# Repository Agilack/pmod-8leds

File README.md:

PMOD 8 Leds
===========

This project is a PMOD prototyping board with 8 LEDs.

 | 
------------------- | -------------------------------

The board connector use a PMOD type 1A pinout. Each available GPIO is
connected to one LED with a component id that reflect signel id (LED D1 is
mapped to signal GPIO1, D2 for GPIO2 ...)
To avoid driving too much current from host ios, a buffer is placed between
connector and LEDs. This buffer add a small latency (~5ns) and limit the
switching frequency to fwe dozen MHz but this seem to be acceptable for
LEDs ;)

Designed with Kicad
-------------------
This board has been designed using Kicad 5.0.2
For a better compatibility and a simplified distribution of this project,
all schematics components are available into a custom project library. It's
the same for board footprints that have been saved into a cutom library. For
3D models, default kicad parts are used (and some display errors can occurs)

 |  | 
------------------------- | ------------------------- | ---------------------------------

License
-------

This project is licensed under a [Creative Commons Attribution-ShareAlike 4.0 International License](http://creativecommons.org/licenses/by-sa/4.0/).

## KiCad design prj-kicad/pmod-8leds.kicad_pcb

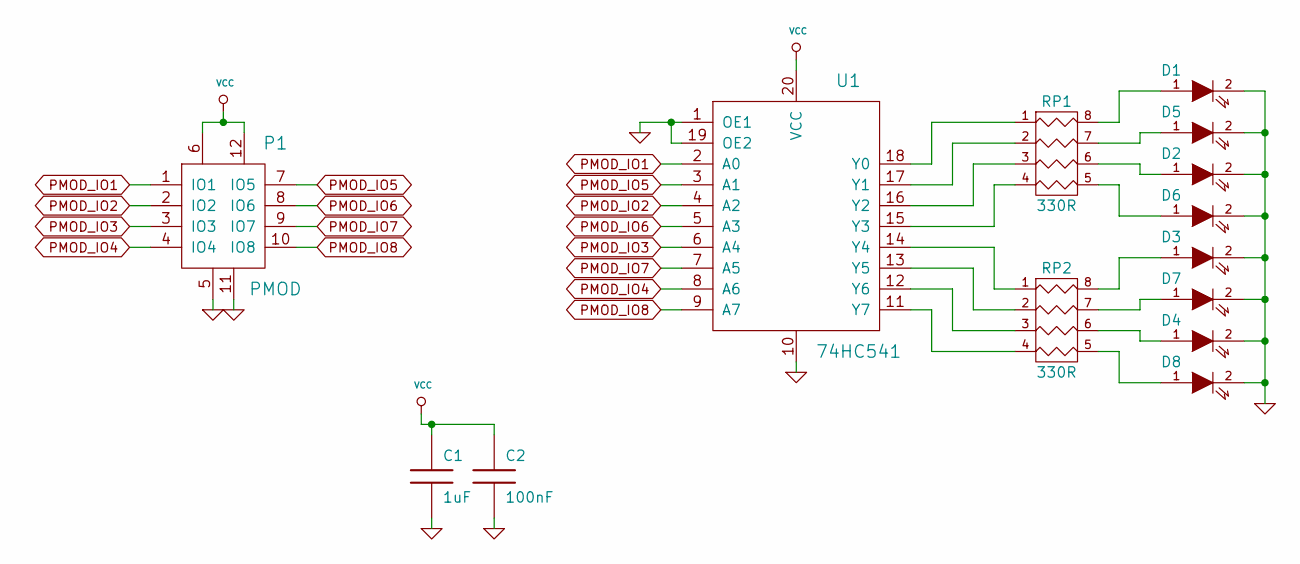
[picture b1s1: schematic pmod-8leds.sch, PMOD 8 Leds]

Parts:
C1: 1uF; SMD0805
C2: 100nF; SMD0603
D1, D2, D3, D4, D5, D6, D7, D8: LED; SMD0805
P1: PMOD; CONN_PMOD-Male
RP1, RP2: 330R; R_4x0603
U1: 74HC541; TSSOP20

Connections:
GND: C1.2, C2.2, D1.2 (K), D2.2 (K), D3.2 (K), D4.2 (K), D5.2 (K), D6.2 (K), D7.2 (K), D8.2 (K), P1.5, P1.11, U1.1 (OE1), U1.10, U1.19 (OE2)
unnamed: D1.1 (A), RP1.8 (R1)
unnamed: D2.1 (A), RP1.6 (R3)
unnamed: D3.1 (A), RP2.8 (R1)
unnamed: D4.1 (A), RP2.6 (R3)
unnamed: D5.1 (A), RP1.7 (R2)
unnamed: D6.1 (A), RP1.5 (R4)
unnamed: D7.1 (A), RP2.7 (R2)
unnamed: D8.1 (A), RP2.5 (R4)
unnamed: RP1.1, U1.18 (Y0)
unnamed: RP1.2, U1.17 (Y1)
unnamed: RP1.3, U1.16 (Y2)
unnamed: RP1.4, U1.15 (Y3)
unnamed: RP2.1, U1.14 (Y4)
unnamed: RP2.2, U1.13 (Y5)
unnamed: RP2.3, U1.12 (Y6)
unnamed: RP2.4, U1.11 (Y7)
PMOD_IO1: P1.1 (IO1), U1.2 (A0)
PMOD_IO2: P1.2 (IO2), U1.4 (A2)
PMOD_IO3: P1.3 (IO3), U1.6 (A4)
PMOD_IO4: P1.4 (IO4), U1.8 (A6)
PMOD_IO5: P1.7 (IO5), U1.3 (A1)
PMOD_IO6: P1.8 (IO6), U1.5 (A3)
PMOD_IO7: P1.9 (IO7), U1.7 (A5)
PMOD_IO8: P1.10 (IO8), U1.9 (A7)
VCC: C1.1, C2.1, P1.6, P1.12, U1.20 (VCC)

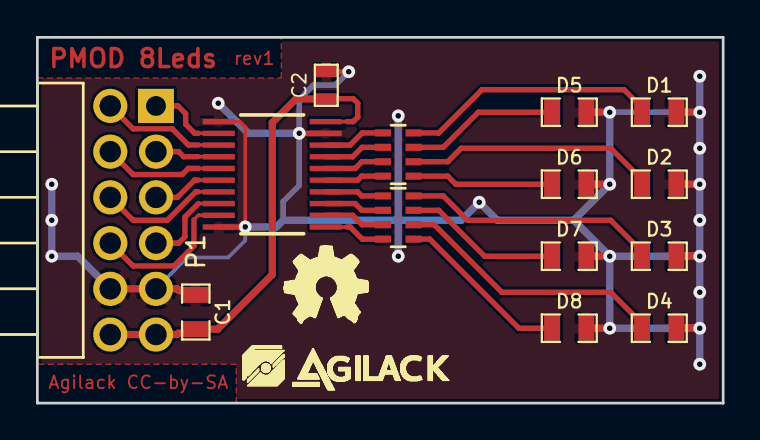
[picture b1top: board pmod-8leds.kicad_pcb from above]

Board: 2 copper layers, 38.1 x 20.3 mm, 16 parts (0 on the bottom side), 26 nets.

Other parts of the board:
agilack-11.5: 450px; logo-agilack-11.5
ohw_logo: VAL**; logo-ohw

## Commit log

2020-06-04 = ADD: Create schematic and pcb routing
2020-06-05 = ADD: Create production files (gerber)
2020-06-09 = UPD: Insert pictures of real board and update readme file

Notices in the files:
README.md:
CC BY-SA 4.0
prj-kicad/pmod-8leds.kicad_pcb:
Agilack CC-by-SA
prj-kicad/pmod-8leds.sch:
License: CC-by-SA 2.0
